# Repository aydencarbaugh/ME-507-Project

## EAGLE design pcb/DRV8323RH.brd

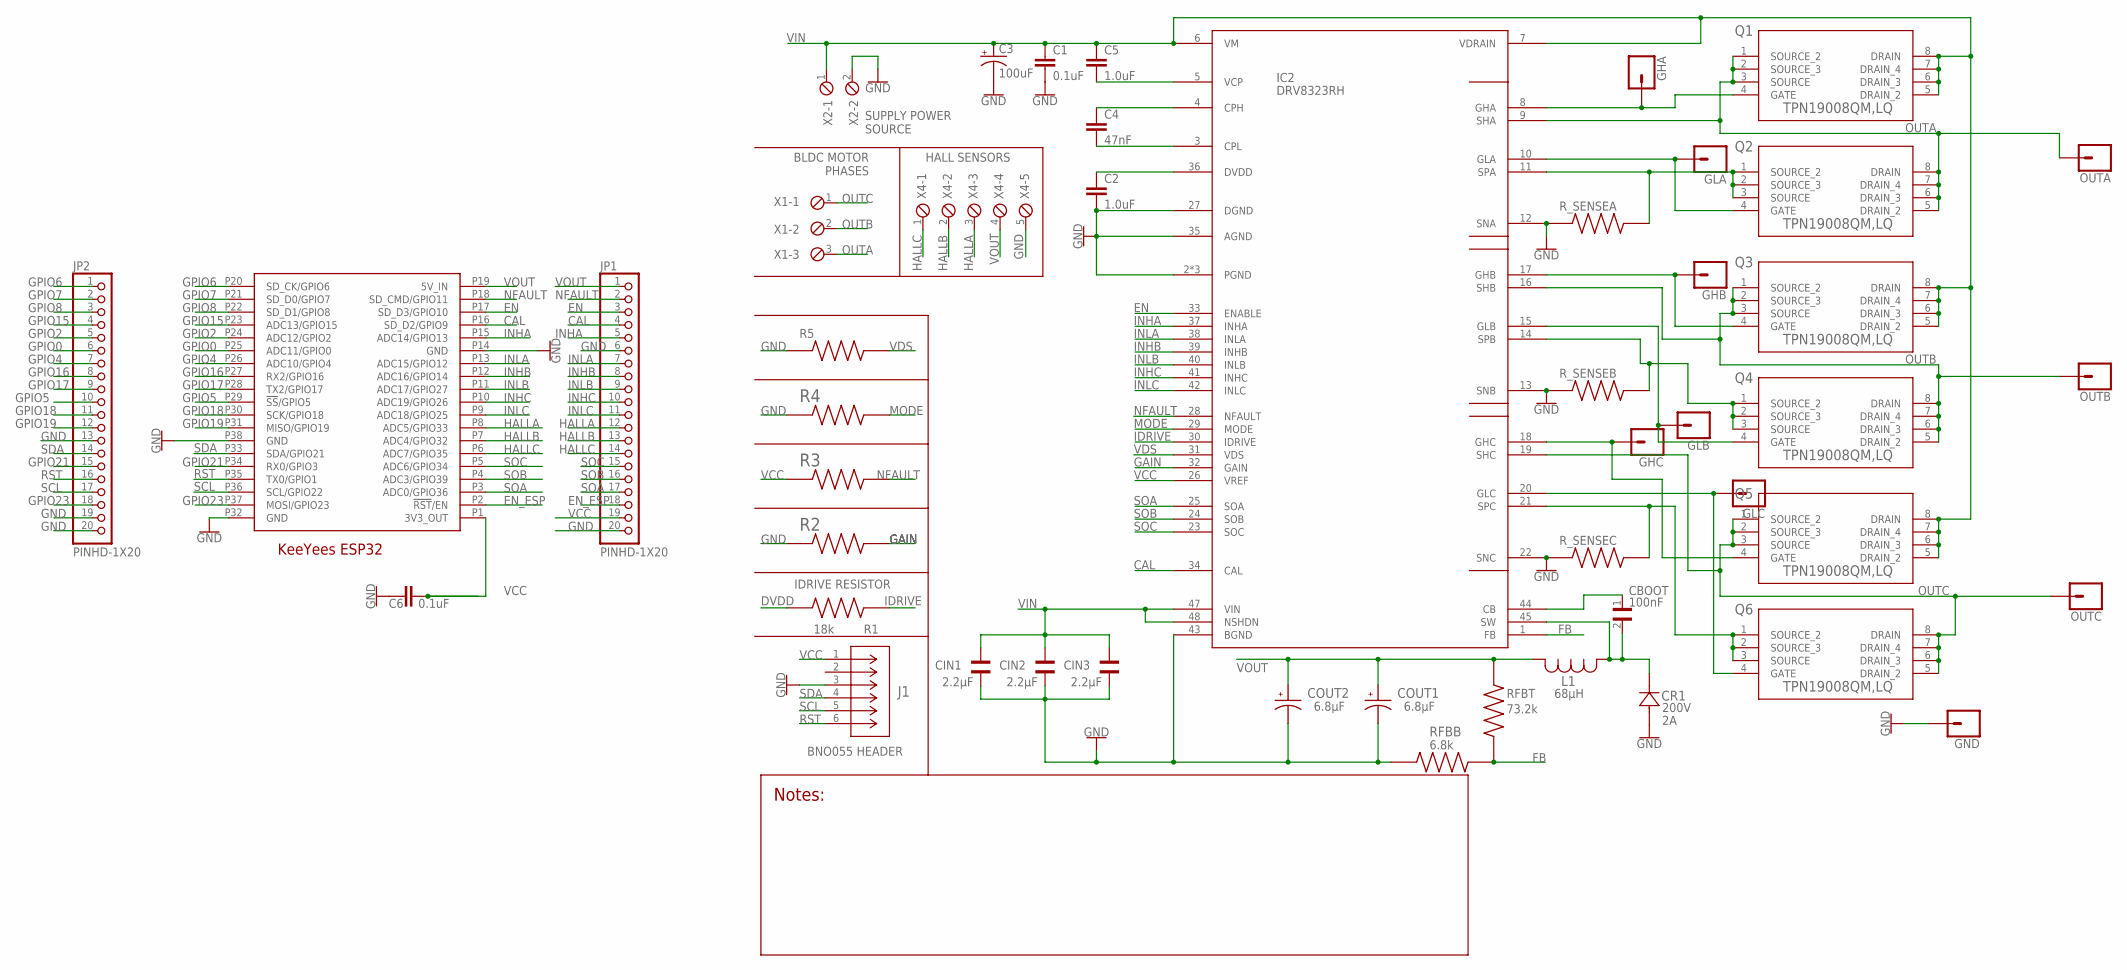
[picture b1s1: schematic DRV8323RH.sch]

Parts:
C1, C6: 0.1uF; 0603
C2, C5: 1.0uF; 0805
C3: 100uF; CPOL-RADIAL-2.5MM-6.5MM
C4: 47nF; 0603
CBOOT: C2012X7R2A104K125AA; CAPC2012X145N
CIN1, CIN2, CIN3: C3225X7R2A225K230AB; CAP_C3225X7R2A225K230AB
COUT1, COUT2: TPSD685K050R0600; CAPPM7343X310N
CR1: SK220ATRDIODE_SK220ATR_SMC-L; DIODE_SK220ATR_SMC-L
GHA: CONN_01_1MM; 1X01_1MM_NO_SILK
GHB: CONN_01_1MM; 1X01_1MM_NO_SILK
GHC: CONN_01_1MM; 1X01_1MM_NO_SILK
GLA: CONN_01_1MM; 1X01_1MM_NO_SILK
GLB: CONN_01_1MM; 1X01_1MM_NO_SILK
GLC: CONN_01_1MM; 1X01_1MM_NO_SILK
GND: CONN_01_1MM; 1X01_1MM_NO_SILK
IC2: DRV8323RH; QFN50P700X700X100-49T515
J1: PPTC061LFBN-RCCONN6_061LFBN-RC_SUL; CONN6_061LFBN-RC_SUL
JP1, JP2: PINHD-1X20; 1X20
L1: SRR1210-680MIND_BOURNS_SRR1210; IND_BOURNS_SRR1210
OUTA: CONN_01_1MM; 1X01_1MM_NO_SILK
OUTB: CONN_01_1MM; 1X01_1MM_NO_SILK
OUTC: CONN_01_1MM; 1X01_1MM_NO_SILK
Q1, Q2, Q3, Q4, Q5, Q6: TPN19008QM,LQ; TSON_ADVANCE_TOS
R1, R5: ERJP06J183V; RES_ERJP06J183V
R2: RMCF0805JT750K; RESC2012X65N
R3: RC0805JR-0710KP; RESC2012X60N
R4: RNCF0805DTE47K0; RESC2012X65N
RFBB: RC1206FR-076K8L; RESC3116X65N
RFBT: RR1220P-7322-D-M; RESC2012X50N
R_SENSEA: CRM2512-FX-R300ELF; RESC6331X80N
R_SENSEB: CRM2512-FX-R300ELF; RESC6331X80N
R_SENSEC: CRM2512-FX-R300ELF; RESC6331X80N
U$1: KEEYEES_ESP32EXT; KEEYEES_ESP32_EXTENDED
X1: SCREWTERM_3P_508; 3POL508
X2: SCREWTERM_2P_508; 2POL508
X4: SCREWTERM_5P_508; 5POL508

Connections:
CAL: IC2.34 (CAL), JP1.4, U$1.P16 (SD_D2/GPIO9)
DVDD: C2.1, IC2.36 (DVDD), R1.1
EN: IC2.33 (ENABLE), JP1.3, U$1.P17 (SD_D3/GPIO10)
EN_ESP: JP1.18, U$1.P2 (!RST!/EN)
FB: IC2.1 (FB), RFBB.2, RFBT.1
GAIN: IC2.32 (GAIN), R2.2
GHA: GHA.1, IC2.8 (GHA), Q1.4 (GATE)
GHB: GHB.1, IC2.17 (GHB), Q3.4 (GATE)
GHC: GHC.1, IC2.18 (GHC), Q5.4 (GATE)
GLA: GLA.1, IC2.10 (GLA), Q2.4 (GATE)
GLB: GLB.1, IC2.15 (GLB), Q4.4 (GATE)
GLC: GLC.1, IC2.20 (GLC), Q6.4 (GATE)
GND: C1.2, C2.2, C3.2 (-), C6.2, CIN1.1, CIN2.1, CIN3.1, COUT1.2, COUT2.2, CR1.2, GND.1, IC2.2 (PGND), IC2.12 (SNA), IC2.13 (SNB), IC2.22 (SNC), IC2.27 (DGND), IC2.35 (AGND), IC2.43 (BGND), IC2.46 (PGND), IC2.49 (PGND), J1.3, JP1.6, JP1.20, JP2.13, JP2.19, JP2.20, R2.1, R4.1, R5.1, RFBB.1, R_SENSEA.1, R_SENSEB.1, R_SENSEC.1, U$1.P14 (GND), U$1.P32 (GND), U$1.P38 (GND), X2.2, X4.5
GPIO0: JP2.6, U$1.P25 (ADC11/GPIO0)
GPIO2: JP2.5, U$1.P24 (ADC12/GPIO2)
GPIO4: JP2.7, U$1.P26 (ADC10/GPIO4)
GPIO5: JP2.10, U$1.P29 (!SS!/GPIO5)
GPIO6: JP2.1, U$1.P20 (SD_CK/GPIO6)
GPIO7: JP2.2, U$1.P21 (SD_D0/GPIO7)
GPIO8: JP2.3, U$1.P22 (SD_D1/GPIO8)
GPIO15: JP2.4, U$1.P23 (ADC13/GPIO15)
GPIO16: JP2.8, U$1.P27 (RX2/GPIO16)
GPIO17: JP2.9, U$1.P28 (TX2/GPIO17)
GPIO18: JP2.11, U$1.P30 (SCK/GPIO18)
GPIO19: JP2.12, U$1.P31 (MISO/GPIO19)
GPIO21: JP2.15, U$1.P34 (RX0/GPIO3)
GPIO23: JP2.18, U$1.P37 (MOSI/GPIO23)
HALLA: JP1.12, U$1.P8 (ADC5/GPIO33), X4.3
HALLB: JP1.13, U$1.P7 (ADC4/GPIO32), X4.2
HALLC: JP1.14, U$1.P6 (ADC7/GPIO35), X4.1
IDRIVE: IC2.30 (IDRIVE), R1.2
INHA: IC2.37 (INHA), JP1.5, U$1.P15 (ADC14/GPIO13)
INHB: IC2.39 (INHB), JP1.8, U$1.P12 (ADC16/GPIO14)
INHC: IC2.41 (INHC), JP1.10, U$1.P10 (ADC19/GPIO26)
INLA: IC2.38 (INLA), JP1.7, U$1.P13 (ADC15/GPIO12)
INLB: IC2.40 (INLB), JP1.9, U$1.P11 (ADC17/GPIO27)
INLC: IC2.42 (INLC), JP1.11, U$1.P9 (ADC18/GPIO25)
MODE: IC2.29 (MODE), R4.2
unnamed: CBOOT.1, IC2.44 (CB)
unnamed: C4.1, IC2.4 (CPH)
unnamed: C4.2, IC2.3 (CPL)
NFAULT: IC2.28 (NFAULT), JP1.2, R3.2, U$1.P18 (SD_CMD/GPIO11)
OUTA: IC2.9 (SHA), OUTA.1, Q1.1 (SOURCE_2), Q1.2 (SOURCE_3), Q1.3 (SOURCE), Q2.5 (DRAIN_2), Q2.6 (DRAIN_3), Q2.7 (DRAIN_4), Q2.8 (DRAIN), X1.3
OUTB: IC2.16 (SHB), OUTB.1, Q3.1 (SOURCE_2), Q3.2 (SOURCE_3), Q3.3 (SOURCE), Q4.5 (DRAIN_2), Q4.6 (DRAIN_3), Q4.7 (DRAIN_4), Q4.8 (DRAIN), X1.2
OUTC: IC2.19 (SHC), OUTC.1, Q5.1 (SOURCE_2), Q5.2 (SOURCE_3), Q5.3 (SOURCE), Q6.5 (DRAIN_2), Q6.6 (DRAIN_3), Q6.7 (DRAIN_4), Q6.8 (DRAIN), X1.1
RST: J1.6, JP2.16, U$1.P35 (TX0/GPIO1)
SCL: J1.5, JP2.17, U$1.P36 (SCL/GPIO22)
SDA: J1.4, JP2.14, U$1.P33 (SDA/GPIO21)
SOA: IC2.25 (SOA), JP1.17, U$1.P3 (ADC0/GPIO36)
SOB: IC2.24 (SOB), JP1.16, U$1.P4 (ADC3/GPIO39)
SOC: IC2.23 (SOC), JP1.15, U$1.P5 (ADC6/GPIO34)
SPA: IC2.11 (SPA), Q2.1 (SOURCE_2), Q2.2 (SOURCE_3), Q2.3 (SOURCE), R_SENSEA.2
SPB: IC2.14 (SPB), Q4.1 (SOURCE_2), Q4.2 (SOURCE_3), Q4.3 (SOURCE), R_SENSEB.2
SPC: IC2.21 (SPC), Q6.1 (SOURCE_2), Q6.2 (SOURCE_3), Q6.3 (SOURCE), R_SENSEC.2
SW: CBOOT.2, CR1.1, IC2.45 (SW), L1.2
VCC: C6.1, IC2.26 (VREF), J1.1, JP1.19, R3.1, U$1.P1 (3V3_OUT)
VCP: C5.2, IC2.5 (VCP)
VDS: IC2.31 (VDS), R5.2
VIN: C1.1, C3.1 (+), C5.1, CIN1.2, CIN2.2, CIN3.2, IC2.6 (VM), IC2.7 (VDRAIN), IC2.47 (VIN), IC2.48 (NSHDN), Q1.5 (DRAIN_2), Q1.6 (DRAIN_3), Q1.7 (DRAIN_4), Q1.8 (DRAIN), Q3.5 (DRAIN_2), Q3.6 (DRAIN_3), Q3.7 (DRAIN_4), Q3.8 (DRAIN), Q5.5 (DRAIN_2), Q5.6 (DRAIN_3), Q5.7 (DRAIN_4), Q5.8 (DRAIN), X2.1
VOUT: COUT1.1, COUT2.1, JP1.1, L1.1, RFBT.2, U$1.P19 (5V_IN), X4.4

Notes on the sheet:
SUPPLY POWER SOURCE
BLDC MOTOR PHASES
BNO055 HEADER
HALL SENSORS
IDRIVE RESISTOR

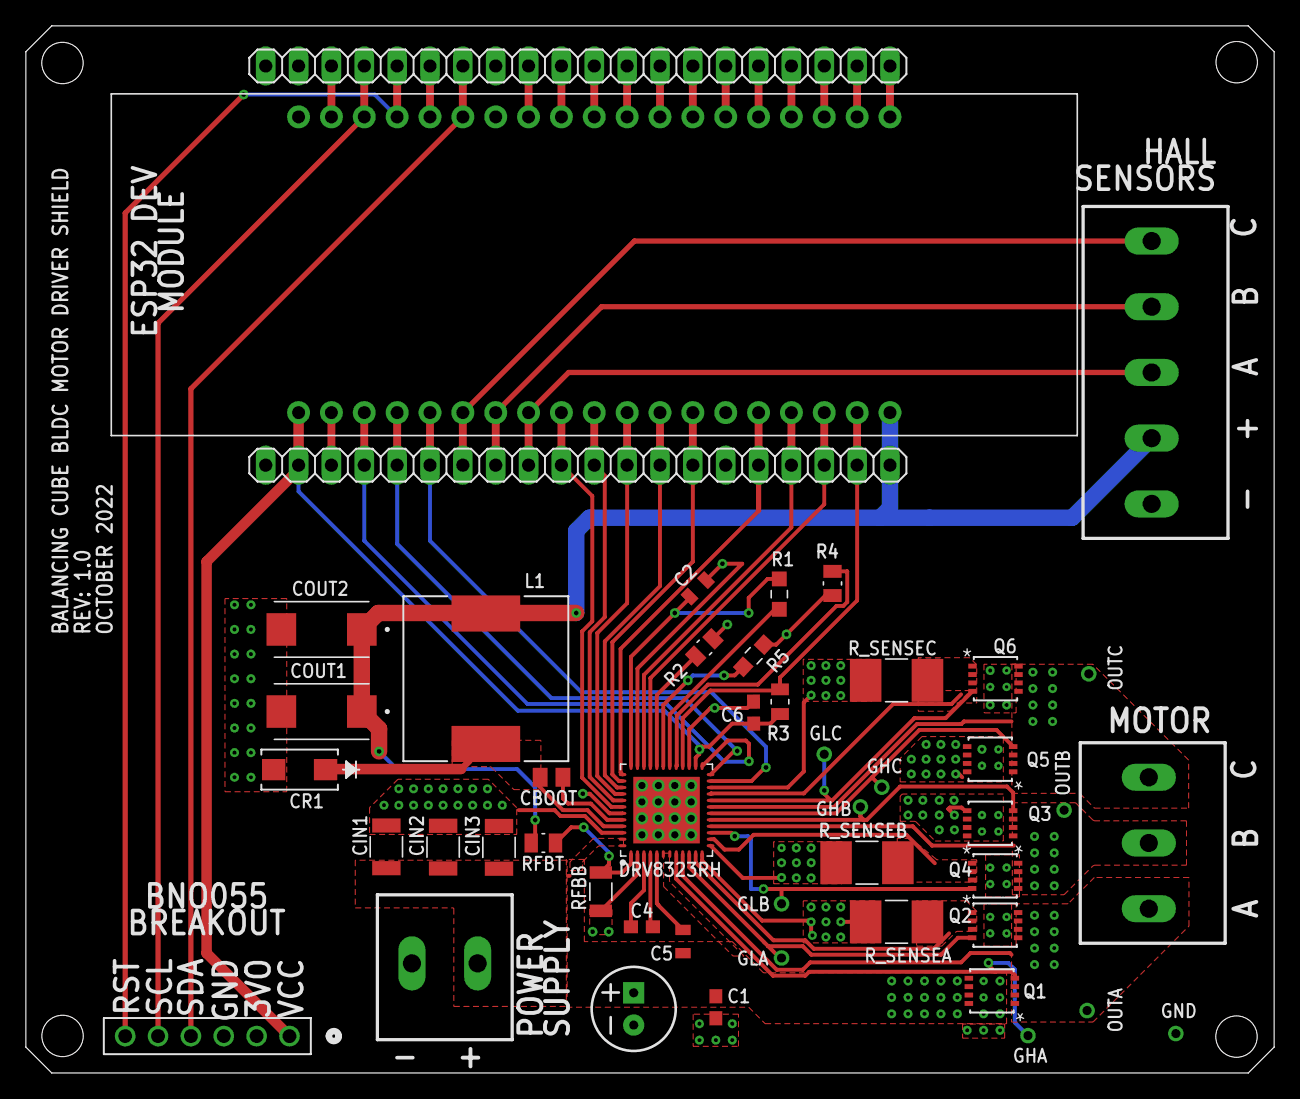
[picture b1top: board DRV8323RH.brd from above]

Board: 2 copper layers, 96.5 x 81.0 mm, 48 parts (0 on the bottom side), 60 nets.

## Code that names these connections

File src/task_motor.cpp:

/** @file task_motor.cpp
 *  This file implements a motor task using a three-phase brushless DC motor
 *  using the DRV8323RH motor driver chip on a custom PCB.
 *  
 *  @author Jarod Lyles
 *  @author Juan Luna
 *  @date   2022-Nov-02 Original file
 *  @date   2022-Dec-05 Modified
 */

#include "task_motor.h"

/** @brief   Task that implements the functionality of a three-phase BLDC motor.
 *  @details Function that sets direction and speed of a three-phase brushless
 *           DC motor for the DRV8323RH motor driver. File sets percent duty
 *           cycle level according to a simple proportional control system.      
 *  @param   p_params A pointer to parameters passed to this task. This 
 *           pointer is ignored; it should be set to @c NULL in the 
 *           call to @c xTaskCreate() which starts this task
 */
void task_motor(void* p_params)
{
    /// Assign GPIO pin 33 to Hall effect sensor input for phase A
    const uint8_t HALL_A_IN = 33;
    /// Assign GPIO pin 32 to Hall effect sensor input for phase B
    const uint8_t HALL_B_IN = 32;
    /// Assign GPIO pin 35 to Hall effect sensor input for phase C
    const uint8_t HALL_C_IN = 35;

    /// Assign GPIO pin 12 to Hall effect sensor output for phase A
    const uint8_t HALL_A_OUT = 12;    // INLC
    /// Assign GPIO pin 14 to Hall effect sensor output for phase B
    const uint8_t HALL_B_OUT = 14;    // INHB
    /// Assign GPIO pin 27 to Hall effect sensor output for phase C
    const uint8_t HALL_C_OUT = 27;    // INLB

    /// Assign GPIO pin 26 to motor brake output 
    const uint8_t INHC = 26;
    /// Assign GPIO pin 25 to motor direction output
    const uint8_t INLC = 25;

    /// Assign GPIO pin 13 to PWM signal output
    const uint8_t INHA = 13;  

    // Motor PWM parameters

    /// Motor PWM frequency; at least 20 kHz
    const uint16_t freq = 50000;
    /// Motor channel number
    const uint8_t channel = 0;
    /// PWM resolution; 8-16 bit available
    const uint8_t resolution = 8;
    /// Converts duty cycle to 8-bit number for ledcWrite function
    float dutyCycle =  255 * setpoint_pwm_shares.get();

    // Configure PWM channels using built-in ledc functions
    ledcSetup(channel, freq, resolution);
    ledcAttachPin(INHA, channel);

    // Set up the brake and direction GPIOs for output
    pinMode(INLC, OUTPUT);
    pinMode(INLC, OUTPUT);

    // Set up the hall sensor inputs GPIOs for input
    pinMode(HALL_A_IN, INPUT);
    pinMode(HALL_B_IN, INPUT);
    pinMode(HALL_C_IN, INPUT);

    // Set up the hall sensor outputs GPIOs for output
    // These are fed into the motor driver
    pinMode(HALL_A_OUT, OUTPUT);
    pinMode(HALL_B_OUT, OUTPUT);
    pinMode(HALL_C_OUT, OUTPUT);
    
    /// Holds the current state of the finite-state machine
    uint8_t state = 0;

    while (true)
    {
        // STATE 0: Wait for input to transition state and start balancing
        if (state == 0)
        {
            // If begin_balancing shares is true
            if (begin_balancing.get ())
            {
                // Lower start-balancing "flag" once actual balancing starts  
                begin_balancing.put(false);
                // Transition to state 1
                state = 1;
            }
        }
        // STATE 1: Run the motor
        else if (state == 1)
        {
            // Turns off the brake
            digitalWrite(INLC, HIGH); 
            // Writes the direction of the motor according to latest share value     
            digitalWrite(INHC, direction_shares.get());
            // Outputs the PWM cycle with calculated duty cycle from controller
            ledcWrite(channel, dutyCycle);  
            
            // The following conditional statements read the input from the 
            // Hall effect sensors on an input pin, then mimic those signals on
            // the output pin that goes into the DRV.
            // We did this for two reasons:
            
            // 1. This allowed us to easily interface with the Hall effect
            // sensors in the motor using our custom board design, whether
            // our custom board worked or not.
            // 2. We read signals from the Hall effect sensors to understand
            // better how they functioned and tired to measure the speed of 
            // the motor from this (though this wasn't implmented).

            if (digitalRead(HALL_A_IN))
            {
                digitalWrite(HALL_A_OUT, HIGH);
            }
            else
            {
                digitalWrite(HALL_A_OUT, LOW);
            }

            if (digitalRead(HALL_B_IN))
            {
                digitalWrite(HALL_B_OUT, HIGH);
            }
            else
            {
                digitalWrite(HALL_B_OUT, LOW);
            }

            if (digitalRead(HALL_C_IN))
            {
                digitalWrite(HALL_C_OUT, HIGH);
            }
            else
            {
                digitalWrite(HALL_C_OUT, LOW);
            }
        }
        // During testing, we found that we needed an extreme low delay to 
        // run the motor correctly. The Hall sensors update very quickly, and
        // if they are not read fast enough, the motor commutation is extremely
        //choppy and does not achieve speed. In future implmentation, 
        // we might want to figure out how to run even faster.
        vTaskDelay(1);
    }
}

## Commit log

2022-12-15 git control testing code

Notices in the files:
parts and their libraries:
SparkFun-Capacitors: Licensing: Creative Commons ShareAlike 4.0 International - https://creativecommons.org/licenses/by-sa/4.0
COPYRIGHT: Copyright (C) 2022 Ultra Librarian. All rights reserved.
